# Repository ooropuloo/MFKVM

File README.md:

# MF KVM

**繁體中文** | [English](README.en.md)

MF KVM 是以 ESP32-P4 為主控、跑 [ESP-KVM](https://github.com/espkvm/espkvm) 韌體的 KVM over IP 小盒子：接上主機的 HDMI 和 USB 之後，就能透過 Wi-Fi 從瀏覽器看主機畫面、操作鍵盤滑鼠，也能按主機的電源和重置鍵。這個 repo 並列兩個設計：`off-the-shelf/` 用買得到的現成板組裝，只自製一片 ATX 小板；`lay-board/` 把所有電路自己布在一片 6 層板上。

**狀態：r8b 已於 2026-11-16 下單打板，板子還沒到。** 沒有焊過、沒有上電，通過的都是檔案和模型層級的檢查，沒有任何一項在硬體上驗證過。

授權見 [LICENSE](LICENSE)：硬體 CERN-OHL-P-2.0、程式 Apache-2.0、文件 CC-BY-4.0。第三方內容另依原本的條款，見 [THIRD_PARTY.md](THIRD_PARTY.md)。

## 目前版本：r8b

6 層單片板，40 × 40 mm，雙面放零件。主控是 ESP32-P4-Module（U1，組裝後手焊），影像用 TC358743（U7，BGA）。外殼是全鋁、無風扇，42 × 42 × 23 mm，Wi-Fi 天線外接。

| 外殼和尺寸 | 和 AA 電池比大小 |
|---|---|
|  |  |

**上面兩張和下面的爆炸圖是 AI 生成的示意圖，不是照片，東西還沒有做出來。** 它們是拿外殼的工程算繪當底圖重畫的，外形、開孔位置和標籤照著工程圖，尺寸標註是另外用程式畫上去的。螢幕畫面、板子上的小零件、材質和光影都是示意，細節以 [`case/stl/`](lay-board/r8b/case/stl/) 和 Gerber 為準。工程算繪在 [r8b 說明](lay-board/r8b/README.md)。

| 正面 | 背面 |
|---|---|
|  |  |

<details>
<summary>零件代號對照表（點開看圖查詢）</summary>

**正面（Top）**

| 代號 | 是什麼 | 用途／備註 |
|---|---|---|
| U1 | ESP32-P4 模組 | 主控加 Wi-Fi，另外買、組裝後手焊，最大熱源 |
| J3 | USB-C | 接被控主機（鍵盤滑鼠、虛擬媒體） |
| J5 | USB-C | 5 V 供電、燒錄、console |
| J6 | SM08B 8P | 接圓形 LCD |
| U14 | ESD 保護 | J5 的 USB 線 |
| U15 + L2 | 降壓 | 3V3 → 1.2 V |
| D1 | ESD 保護 | HDMI CEC |

**背面（Bottom）**

| 代號 | 是什麼 | 用途／備註 |
|---|---|---|
| J2 | HDMI | 影像輸入 |
| U7 | TC358743 BGA | HDMI 轉 CSI，最燙的晶片 |
| J7 | microSD | 虛擬媒體、儲存 |
| U16 | TPS259531 eFuse | 5 V 輸入保護，下單要核對方向 |
| U2 + L1 | 降壓 | 5 V → 3V3 |
| U4 | LDO | 3V3 → 2.5 V |
| U6 | TCA9517A | HDMI DDC 準位轉換 |
| U3、U8、U9 | ESD 保護 | J3 的 USB 線、HDMI TMDS |
| U10、U11、U12 | 光耦 | ATX 電源、重置、LED |
| J4 | SM06B 6P | 接 ATX 前面板 |
| J8 | U.FL | 接 Wi-Fi 天線（用線接到外殼上的 SMA 座） |
| Y1 | 27 MHz 振盪器 | U7 的時脈 |
| Q1 | P 通道 MOSFET | microSD 電源開關 |
| R68 + C72、C73 | 0.47 Ω 加兩顆 22 µF | 5 V 阻尼，取代 r7f 的 330 µF C69 |

電阻、電容太多沒有列，完整清單見 [`BOM_JLC.csv`](lay-board/r8b/fab_r8b/BOM_JLC.csv)。

</details>

板子的兩張圖是從板檔算繪的，不是照片。板檔沒有 3D 模型，零件是依外形和高度畫的方塊。

爆炸示意圖（AI 生成）。由上到下是上蓋、圓形 LCD、鋁散熱板、電路板、底殼。螢幕的線穿過散熱板的方孔接到板子角落的 J6。

| 項目 | 規格 |
|---|---|
| 板子 | 40 × 40 mm，6 層，1.2 mm，JLC06121H-3313，三顆安裝孔 |
| 外殼 | 42 × 42 × 23 mm，6061 鋁 CNC、黑色陽極，無風扇 |
| 表面溫度（模型） | 室溫 25 °C、一般負載下最高約 51.5 °C |
| 主控 | ESP32-P4-Module 基本款（SKU 28101，16MB、天線從焊盤引出），內建 ESP32-C6，2.4 GHz Wi-Fi |
| 天線 | 板上 U.FL，轉 SMA 到外殼左牆，外接天線 |
| 影像 | TC358743XBG，HDMI 轉 CSI |
| 螢幕 | 1.28 吋圓形 LCD（選配） |
| 供電 | Type-C，要能供 1.5 A 以上 |
| 打板包 | [`lay-board/r8b/fab_r8b/`](lay-board/r8b/fab_r8b/)，Gerber zip sha256 開頭 `3613530e` |

### 這版改了什麼（相對 r7f）

| 項目 | 改了什麼 |
|---|---|
| 板子尺寸 | 40 × 45 → 40 × 40 mm，安裝孔 4 顆 → 3 顆 |
| 5 V 阻尼 | 拿掉 330 µF 的 C69，R68 改成 0.47 Ω，新增 C72、C73（22 µF 0805） |
| 外殼 | 由「鋁上蓋＋塑膠底殼＋外接風扇導管」改成全鋁、無風扇，42 × 42 × 23 mm |
| 天線（r8b） | 改外接：外殼左牆開 SMA 孔，U.FL 轉 SMA 線接板子背面的 J8 |
| 板邊淨空（r8b） | SD_CMD 的兩顆過孔和 ATX_LED 走線往板內移到離板邊 0.40 mm 以上 |
| 高度夾持（r8b） | 上蓋的柱子不再壓板子，改用泡棉墊圈 |
| HDMI 開孔（外殼，2026-11-16） | 由矩形改成 HDMI 座的外形，上窄下寬（座焊在板子背面）。板子沒有改 |

TMDS、CSI、USB 的走線和 r7f 相同；r8 → r8b 零件位置、BOM、CPL 都沒有變，108 個網路只有 4 個的銅不同。

**板廠生產時改了阻抗線的線寬：** 100 Ω 線 5.0/7.8 → 4.7/8.1 mil，USB 90 Ω 線寬 7.09 → 6.37 mil，中心距和疊構不變。所以實體板的這幾條線和 repo 裡的 Gerber 不同。用本專案的解算器代回去，都還在 ±10 % 內，見 [`IMPEDANCE_AS_BUILT.md`](lay-board/r8b/IMPEDANCE_AS_BUILT.md)。

### 驗證到哪裡

| 已通過（檔案和模型層級） | 結果 |
|---|---|
| ERC、DRC | ERC 通過；DRC 0 錯誤、0 未連線，29 個警告逐項接受 |
| 電氣規則、熱插拔、輸入濾波、參考層、差動對間距、CSI 過孔、手焊間距、阻抗、零件本體 | 全部通過 |
| 板子故意放錯測試 | 124 項全部抓到 |
| 外殼幾何 | 126 項通過；故意放錯 25 項（含對照組）全部符合預期 |
| 獨立複審（r8） | 板子有條件可送；外殼的 1 項嚴重、3 項主要問題在 r8b 處理或由使用者裁決結案。r8b 沒有再做一次獨立複審 |

**沒有驗證：** 還沒有實體板，EMI、RF／RSSI、影像、USB、Wi-Fi、溫度都沒測過。熱模型在 r8b 沒有重跑。韌體只編譯過，沒有燒過。天線線、天線、泡棉墊圈、導熱材料都還沒選定料號。

**現在的進度：** 2026-11-16 下單，等板子。到貨後照 [`BRINGUP_CHECKLIST.md`](lay-board/r8b/BRINGUP_CHECKLIST.md) 上電。

**完整資料：** [r8b 說明](lay-board/r8b/README.md)、[R8B 改版報告](lay-board/r8b/R8B_REPORT.md)、[R8 改版報告](lay-board/r8b/R8_REPORT.md)、[獨立複審](lay-board/r8b/REVIEW_r8.md)、[熱分析](lay-board/r8b/thermal/THERMAL_R8.md)。上一版 r7f 的資料留在 [`lay-board/r7f/`](lay-board/r7f/README.md)。

## 較早的設計（ARCHIVE）

以下保留當時的內容當紀錄，都不是目前版本。`lay-board/` 這欄是 r5，那張單已經取消。

| | [`off-the-shelf/`](off-the-shelf/README.md)（現成料，第三版） | [`lay-board/`](lay-board/README.md)（客製板，第二版 r5） |
|---|---|---|
| **外殼尺寸** | 75.0 × 38.05 × 26.73 mm | 44 × 44 × 20 mm |
| **體積** | 76 cm³ | 39 cm³ |
| **買什麼** | DFRobot FireBeetle 2 ESP32-P4（DFR1172）、Geekworm C790、Waveshare 1.9 吋 LCD、Würth 50 mm 15-pin 排線（接點異面、同面各 1）、改過不接 VBUS 的 USB 線、Ø0.64 銅線、JST SH 線、螺絲、5 V 電源 | Waveshare ESP32-P4-Module-U（IPEX）、FPC 天線、1.28 吋圓形 LCD、自製 SHR-08 和 SHR-06 線、M2 × 16 螺絲 4 支 |
| **打什麼板** | 2 層 ATX 小板 rev B，11.05 × 35.4 mm（`fab_atx_b/`），尚未下單 | 6 層 40 × 40 mm 主板加雙面 PCBA，含 BGA（`fab_r5/`），JLC 審查中、未付款 |
| **印什麼** | 底殼、上蓋、C790 橋架、排線捲線棒、ATX 焊接墊片（建議 PETG） | 底殼、上蓋 |
| **韌體** | ESP-KVM `0893eef`，加 ST7789 修補與 ATX 修補（兩支 patch），只編譯過 | ESP-KVM `0893eef`，加開機預設值修補與 ATX 修補（兩支 patch），只編譯過。ATX 預設關閉，到 console 打開，見 `lay-board/firmware/BUILD_v2.md` |
| **主要風險** | 排線斜捲 45° 沒人測過、回報僅約 9 fps、ATX 小板焊死後要斜著裝 | 首版 6 層加 BGA 有錯就要重打、阻抗只有公式估算、最壞公差有 4 對本體可能相碰 |
| **狀態** | 只有設計，零件未買 | 打板包只能送 CAM 預審，還不能算放行 |
| **什麼時候選它** | 想先驗證功能、不想打 6 層板和焊 BGA、接受比較大的盒子。目前建議當驗證機，也能先驗證兩邊共用的韌體 | 要最小的外形，或要走正式小型產品，且願意承擔首版改板 |

每個設計的 README 都有 **「還缺什麼」** 清單，列出下單前和實機要做的事：[off-the-shelf](off-the-shelf/README.md#還缺什麼)、[lay-board](lay-board/README.md#還缺什麼)。

## 3D 頁面

每個資料夾裡有一份 HTML，下載後用瀏覽器開就能看（3D 需要連上網路載入 three.js）：

| 設計 | 檔案 |
|---|---|
| lay-board | [`lay-board/kvm-mini.html`](lay-board/kvm-mini.html) |
| off-the-shelf | [`off-the-shelf/v3.html`](off-the-shelf/v3.html) |

## 不在這個 repo 的東西

- **第一版（NANO 模組疊自製底板）：** 排針位置錯，已放棄，沒有放進來。
- **舊打板包：** `fab`、`fab_new`、`fab_r2`～`fab_r4`、`fab_atx` 都不能用，原因寫在各 README。
- **建置輸出：** ESP-KVM clone、build 目錄、映像檔、建置 log。重新編譯的方法在各 README。
- **第三方原始檔：** NANO 官方 CAD、ExoAnchor 壓縮檔、FireBeetle STEP。來源見 [THIRD_PARTY.md](THIRD_PARTY.md) 和 `off-the-shelf/research/`。

## 常用檢查（在 repo 根目錄）

```sh
python lay-board/tools/maskcheck.py lay-board/fab_r5/p4_kvm_mini_gerber.zip
python lay-board/tools/holecheck.py lay-board/fab_r5/p4_kvm_mini_gerber.zip
sh lay-board/tools/check.sh out/final.ses     # 要 KiCad，路徑用 KICAD_CLI、KICAD_TOOL_HOME 覆寫
python lay-board/tools/bodycheck.py lay-board/out
python lay-board/tools/maskcheck.py off-the-shelf/fab_atx_b/mf_kvm_atx_gerber.zip
python lay-board/tools/holecheck.py off-the-shelf/fab_atx_b/mf_kvm_atx_gerber.zip
```

`.gitattributes` 設定 `* -text`，檔案逐位元組保存，不轉換行尾，所以 Gerber 雜湊不會變，`.sh` 也不會變成 CRLF。

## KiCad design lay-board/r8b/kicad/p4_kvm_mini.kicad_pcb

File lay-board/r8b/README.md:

# MF KVM lay-board r8b

目前的板子版本。6 層 40 × 40 mm，ESP32-P4-Module（U1，手焊）加 TC358743（U7，BGA）。r8 由 r7f 改版，把板子從 40 × 45 縮到 40 × 40 mm，外殼改成全鋁、無風扇、42 × 42 × 23 mm；r8b 再把三處走線往板內移、天線改外接。

**狀態：2026-11-16 已下單打板，板子還沒到。** 沒有焊過、沒有上電，通過的都是檔案和模型層級的檢查，沒有任何一項在實機驗證過。

**實體板有一處和這裡的 Gerber 不同：** 板廠審核時把阻抗線改細、中心距不變（100 Ω 線 5.0/7.8 → 4.7/8.1 mil，USB 90 Ω 線寬 7.09 → 6.37 mil）。數字和核對結果在 [`IMPEDANCE_AS_BUILT.md`](IMPEDANCE_AS_BUILT.md)。

| 項目 | 值 |
|---|---|
| Gerber zip sha256 | `3613530e5c3256c378794c367a53c94c30cd249da4c4403c4d094f22236d9397` |
| 外形 | 40.0 × 40.0 mm，四角 1.5 mm 倒角，三顆 2.2 mm 鍍通安裝孔 |
| 層數、厚度 | 6 層，1.2 mm，外層 1 oz |
| 疊構 | JLC06121H-3313，阻抗控制 |
| 最小線寬線距 | 0.09 mm |
| 過孔 | 0.4 / 0.2 mm，Epoxy Filled & Capped |
| 絲印版本 | R8B |
| 供電 | Type-C，要能供 1.5 A 以上 |

每次重跑 release，zip 的 sha 都會變，設計沒有改也一樣。判斷兩包是否相同要用 `tools/gerber_equal.py` 比幾何。

## 圖

### 示意圖（AI 生成）

| 外殼和尺寸 | 和 AA 電池比大小 |
|---|---|
|  |  |

**這三張是 AI 生成的示意圖，不是照片，也不是從 CAD 直接算繪的。** 做法是拿下面的工程算繪當底圖，請生圖模型重畫成棚拍質感；尺寸標註是另外用程式畫上去的。對照過的項目：外形比例、上蓋和底殼之間的銀色分隔線、SMA 座和 USB-C 開孔的位置、各面的標籤、爆炸圖的疊放順序、螢幕的線穿過散熱板方孔接到 J6、兩個 USB-C 座分在左邊和前緣。不準的地方：螢幕畫面是示意（不是實際韌體畫面，位址是範例）、板子上模組周圍的小零件不是逐顆對應、材質和光影是想像的。要看準確的幾何用下面的工程算繪、`case/stl/` 和 Gerber。

### 工程算繪

**下面都是電腦算繪，不是照片。** 板子還沒有做出來。零件是依外形尺寸和高度畫的方塊，顏色只用來分類。

| 正面 | 背面 |
|---|---|
|  |  |

| 外殼組裝 | 外殼爆炸 |
|---|---|
|  |  |

阻抗控制走線的位置：

## 和 r7f 的差別

- 板子 40 × 45 → 40 × 40 mm。安裝孔 4 顆 → 3 顆。
- 5 V 阻尼：330 µF 的 C69 拿掉，R68 改成 0.47 Ω，新增 C72、C73（22 µF 0805）。
- 外殼由「鋁上蓋＋塑膠底殼＋外接風扇導管」改成全鋁、無風扇。
- r8b：SD_CMD 的兩顆過孔和 ATX_LED 走線往板內移到離板邊 0.40 mm 以上；天線改外接，外殼左牆開 SMA 孔；上蓋的柱子不再壓板子，改用泡棉墊圈。
- 外殼追加修改（2026-11-16，板子沒改）：底殼前牆的 HDMI 開孔由矩形改成 HDMI 座的外形，上窄下寬，因為座焊在板子背面、倒掛在板子下方。切角尺寸原廠圖面沒有標，發加工前要量實物，見 `R8B_REPORT.md` 第 5b 節。
- TMDS、CSI、USB 的走線和 r7f 相同。

細節看 `R8_REPORT.md` 和 `R8B_REPORT.md`。

## U1：主控模組（不在打板的 BOM 裡，要另外買、自己手焊）

| 項目 | 值 |
|---|---|
| 廠牌、型號 | Waveshare（微雪）ESP32-P4-Module |
| SKU | 28101 |
| Flash 版本 | **16MB** |
| 天線版本 | **焊盤引出版**（英文站叫 Onboard IPEX connector = Without） |
| 模組內容 | ESP32-P4NRW32X（內含 32 MB PSRAM）加 ESP32-C6（2.4 GHz Wi-Fi、藍牙） |
| 尺寸、接腳 | 25 × 25 mm，城堡焊盤，腳距 1 mm，88 腳 |

同一個商品頁還有三個版本，都不要選：

| 版本 | 為什麼不要 |
|---|---|
| IPEX 接口版（ESP32-P4-Module-U） | 天線訊號改走模組上的 IPEX 座，不從焊盤出來，板子背面的 J8 會沒有訊號 |
| 32MB | 韌體是照 16 MB 編的，燒到 32 MB 模組沒有測過 |
| 32MB 加 IPEX | 上面兩個問題都有 |

板子把模組第 2 腳（LNA_OUT）用 50 Ω 走線拉到背面的 J8（U.FL 座），再用線接到外殼上的 SMA 天線。焊盤引出版的 RF 訊號經模組上的 **R99（0 Ω）** 送到第 2 腳，R99 不能拆。模組本身沒有天線，而 Wi-Fi 是這台唯一的網路。

### 板子用到的模組腳位

| 功能 | 模組腳位 → 網路名 |
|---|---|
| 電源 | 84、85、86 → 3V3；1、3、15、33、40、47、52、83 → GND；87 → ESP_EN |
| 天線 | 2 → LNA_OUT（到 J8） |
| HDMI 擷取（MIPI CSI，來自 TC358743） | 41／42 → CSI_D0_N／P；43／44 → CSI_CK_P／N；45／46 → CSI_D1_N／P |
| TC358743 控制 | 22 → I2C_SDA；23 → I2C_SCL；32 → TC_RST（GPIO 23） |
| USB 到被控主機（J3） | 48 → USB_DN；49 → USB_DP |
| USB 燒錄和 log（J5） | 50 → USB2_DN；51 → USB2_DP（GPIO 24／25） |
| microSD（J7） | 67–70 → SD_D0–D3；71 → SD_CLK；72 → SD_CMD；73 → SD_PWR_N（GPIO 45）；66 → LDO_VO4 |
| 圓形 LCD（J6） | 24 → LCD_DIN；25 → LCD_CLK；26 → LCD_CS；27 → LCD_DC；28 → LCD_RST（GPIO 9–13） |
| ATX（J4） | 19 → ATX_PWR（GPIO 4）；20 → ATX_RST（GPIO 5）；17 → ATX_LED（GPIO 2） |
| 其他 | 18 → HOST_VBUS_DIV；62 → BOOT（TP1）；64／65 → U0_TX／U0_RX（TP3／TP4）；4／5／9／10 → C6_RXD／TXD／IO9／IO8（測試點） |

### 手焊注意

- **第 24、25 腳不要拖焊**：旁邊緊貼 R80、R81（0201，33 Ω，焊盤間距 0.387 mm）。烙鐵不要往 J6 方向帶，錫從模組那一側收。
- **第 67–72 腳不要往板子左側拖**：R79 離第 70 腳約 1 mm。
- 焊完用放大鏡看 R80、R81 還在、沒有連錫或立碑。

## 板子以外還要準備的

| 項目 | 規格 | 備註 |
|---|---|---|
| U1 模組 | 見上一節 | 每片板一顆 |
| U.FL 轉 SMA 穿牆線 | U.FL（IPEX MHF1）對標準 SMA 母座，長約 50–100 mm | 外殼照六角 8 mm、孔 6.5 mm、壓接套管 Ø5 × 10 mm 設計。料號沒有選定 |
| 2.4 GHz 天線 | 標準 SMA 公頭，底座直徑不超過 10 mm | 不是 RP-SMA。料號沒有選定 |
| Type-C 電源 | 5 V，1.5 A 以上 | 1.0 A 以下的埠在全負載下起不來（`fab_r8b/coldstart_r8.txt`） |
| USB 轉 UART 線 | 3.3 V，115200 | 開機階段的 log 只從 UART0 測試點出來 |
| 圓形 LCD（選配） | GC9A01，240 × 240，接 J6 | 不接也能開機 |
| ATX 線（選配） | JST SH 1.0 mm 6 pin，接 J4 | 韌體預設關閉 ATX，量測過才接主機板 |
| 外殼 | 6061 鋁 CNC，圖檔在 `case/stl/` | 接觸面不陽極，清單在 `case/stl/case_spec.json` 的 `masked` |
| 螺絲、泡棉墊圈 | M2 × 16 三顆；墊圈外徑 3.6、內徑 2.2、厚 1.5 mm 三片 | 墊圈料號沒有選定 |
| 導熱材料 | 模組屏蔽罩上方的填充；TC358743 下方凸台的導熱墊（間隙約 0.5 mm） | 料號沒有選定 |

第一次上電的步驟在 [`BRINGUP_CHECKLIST.md`](BRINGUP_CHECKLIST.md)。它是照文件排的，還沒有在實機上走過。

## 內容

| 路徑 | 說明 |
|---|---|
| `R8_REPORT.md`、`R8B_REPORT.md` | 改版報告，先看 R8B |
| `REVIEW_r8.md` | 獨立複審 |
| `MUTATION_REPORT.txt` | 故意放錯測試結果 |
| `IMPEDANCE_AS_BUILT.md` | 阻抗線的設計值和板廠生產值 |
| `BRINGUP_CHECKLIST.md` | 到貨當天的檢查表 |
| `fab_r8b/` | 打板包：Gerber、BOM、CPL、佈局圖和線路圖 PDF、阻抗表、各項檢查輸出 |
| `kicad/` | KiCad 原始檔 |
| `case/` | 外殼產生與檢查程式、STL／STEP、算繪圖 |
| `firmware/` | 韌體建置說明與修補。不放編好的映像 |
| `thermal/` | 熱分析報告 |
| `report_r8/` | r7f→r8、r8→r8b 的差異比對，冷啟動圖 |
| `gen_mini.py`、`layout.py`、`tools/`、`data/` | 產生板子和跑檢查的程式、布線資料 |

`fab_r8b/README.md` 是打板時的說明，內容停在下單之前，請以本頁為準。

和 `r7f/` 比，這裡沒有 `pdf/` 那一套整理過的報告，也沒有 `out/` 的中間檔。

規格書版權屬原廠，沒有放在這裡。要重跑工具，用環境變數指定路徑：`KICAD_CLI`（預設 `kicad-cli`）、`KICAD_TOOL_HOME`、`FREEROUTING_JAR`、`CASE_PY`、`CHROME`。這些工具是從原本的工作目錄複製過來的，路徑改成環境變數後只做過語法檢查，沒有在這裡完整跑過。

## 下單時必做

- 貼片預覽核對 U16（eFuse）第 1 腳：底視圖左下角，靠 C71／R71／R72。轉 180° 會讓 VBUS 短路到 GND。
- 其他方向標為 UNKNOWN 的零件要逐顆看，對照 `fab_r8b/CPL_pin1_check.md` 和 `fab_r8b/CPL_polarity_pin1_r8.md`。
- 過孔選 Epoxy Filled & Capped，不要選阻焊塞孔。
- 拼板要自己指定：四個邊都有東西貼著板邊，後緣不要放郵票孔或 V-cut，郵票孔殘料不能凸出 40.00 mm 外形。

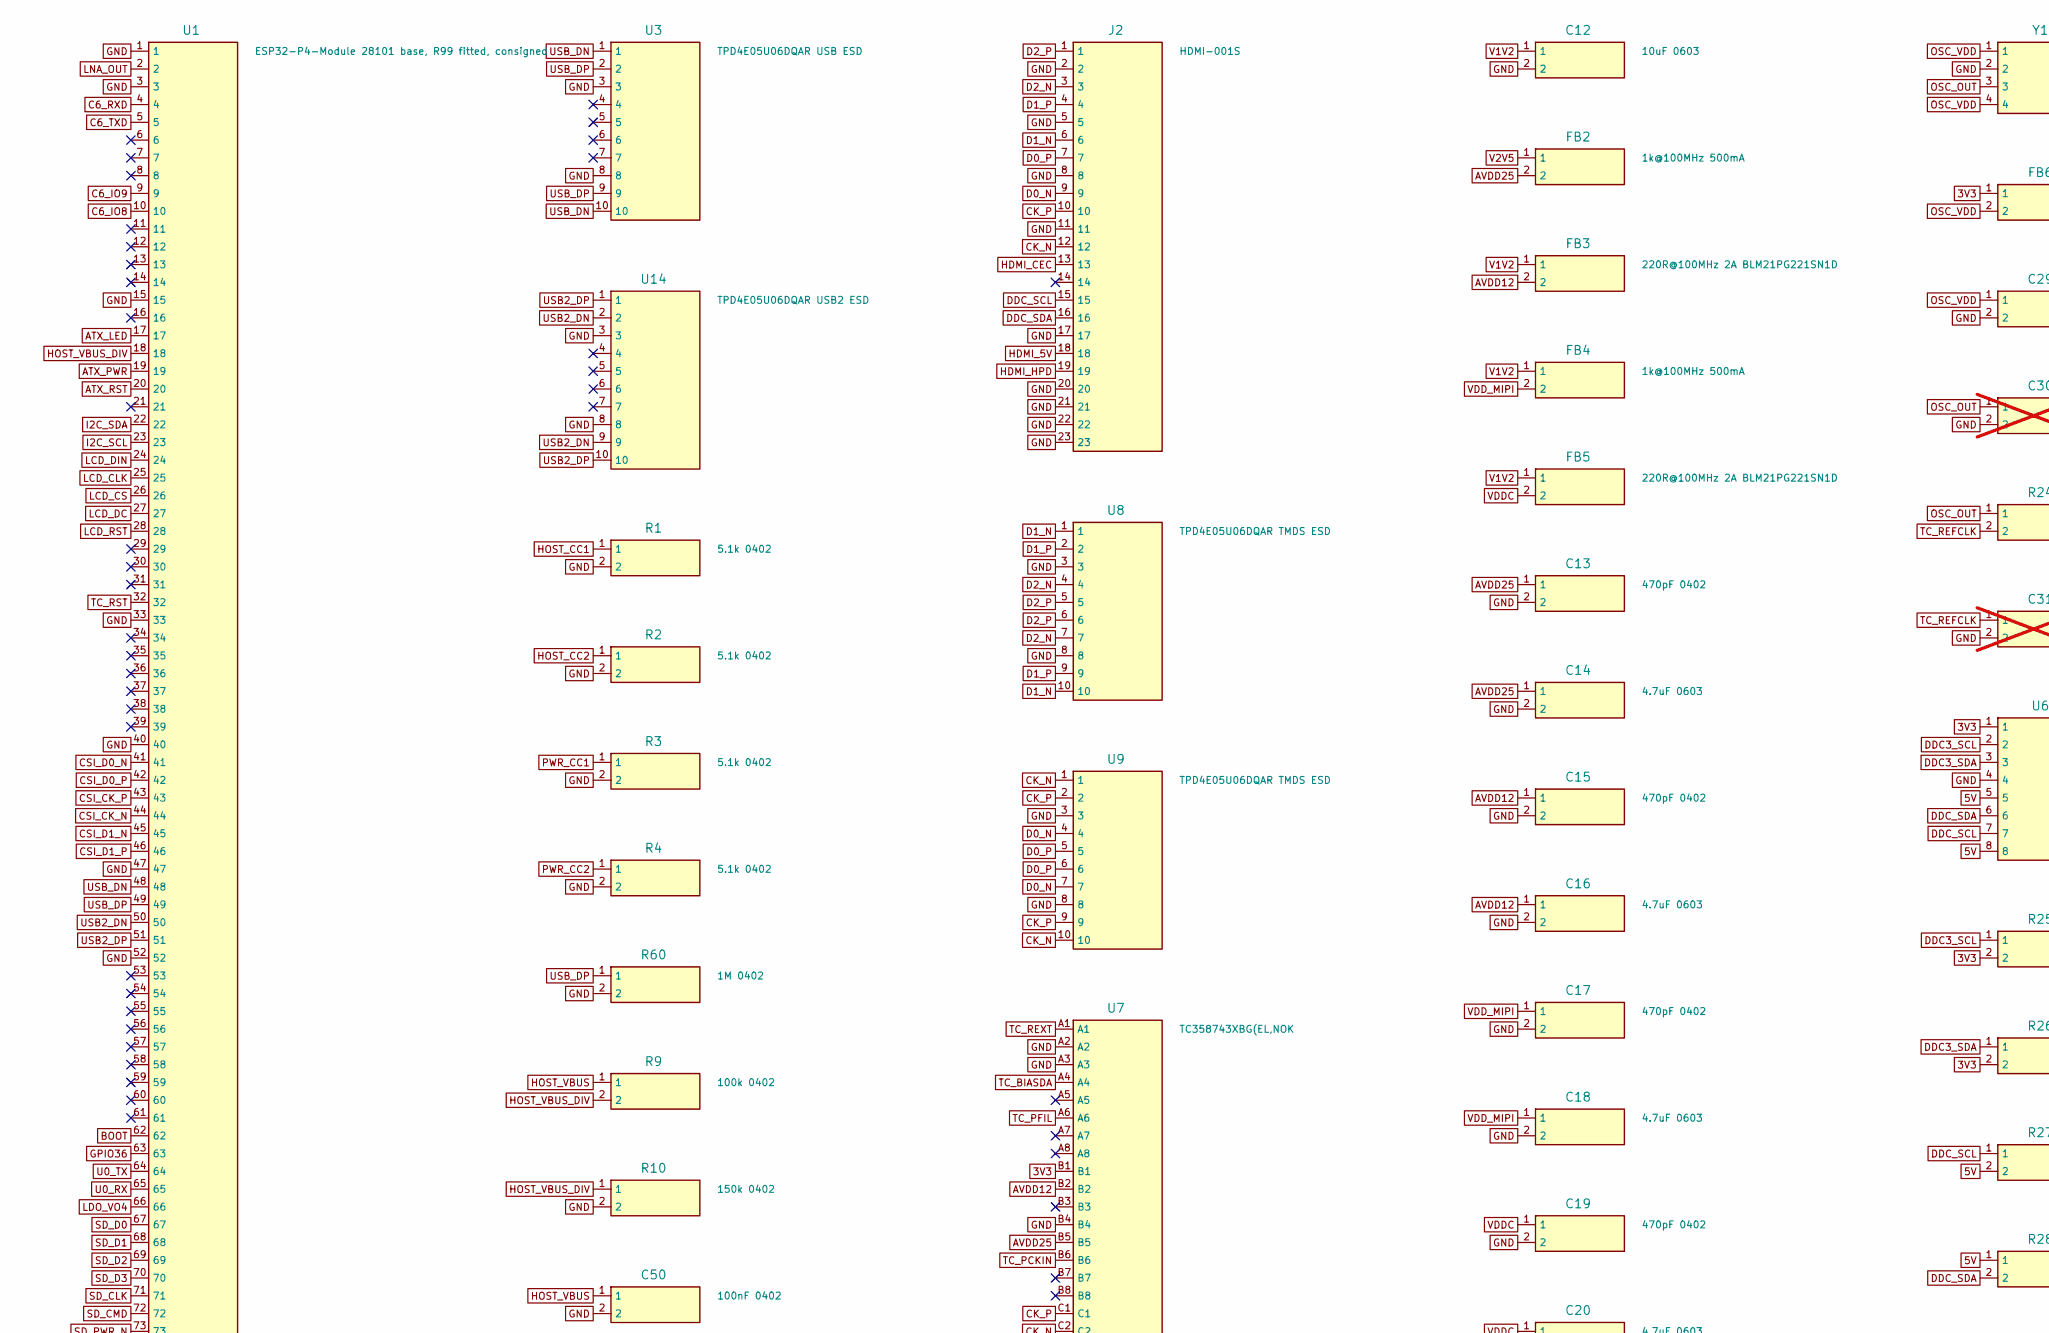
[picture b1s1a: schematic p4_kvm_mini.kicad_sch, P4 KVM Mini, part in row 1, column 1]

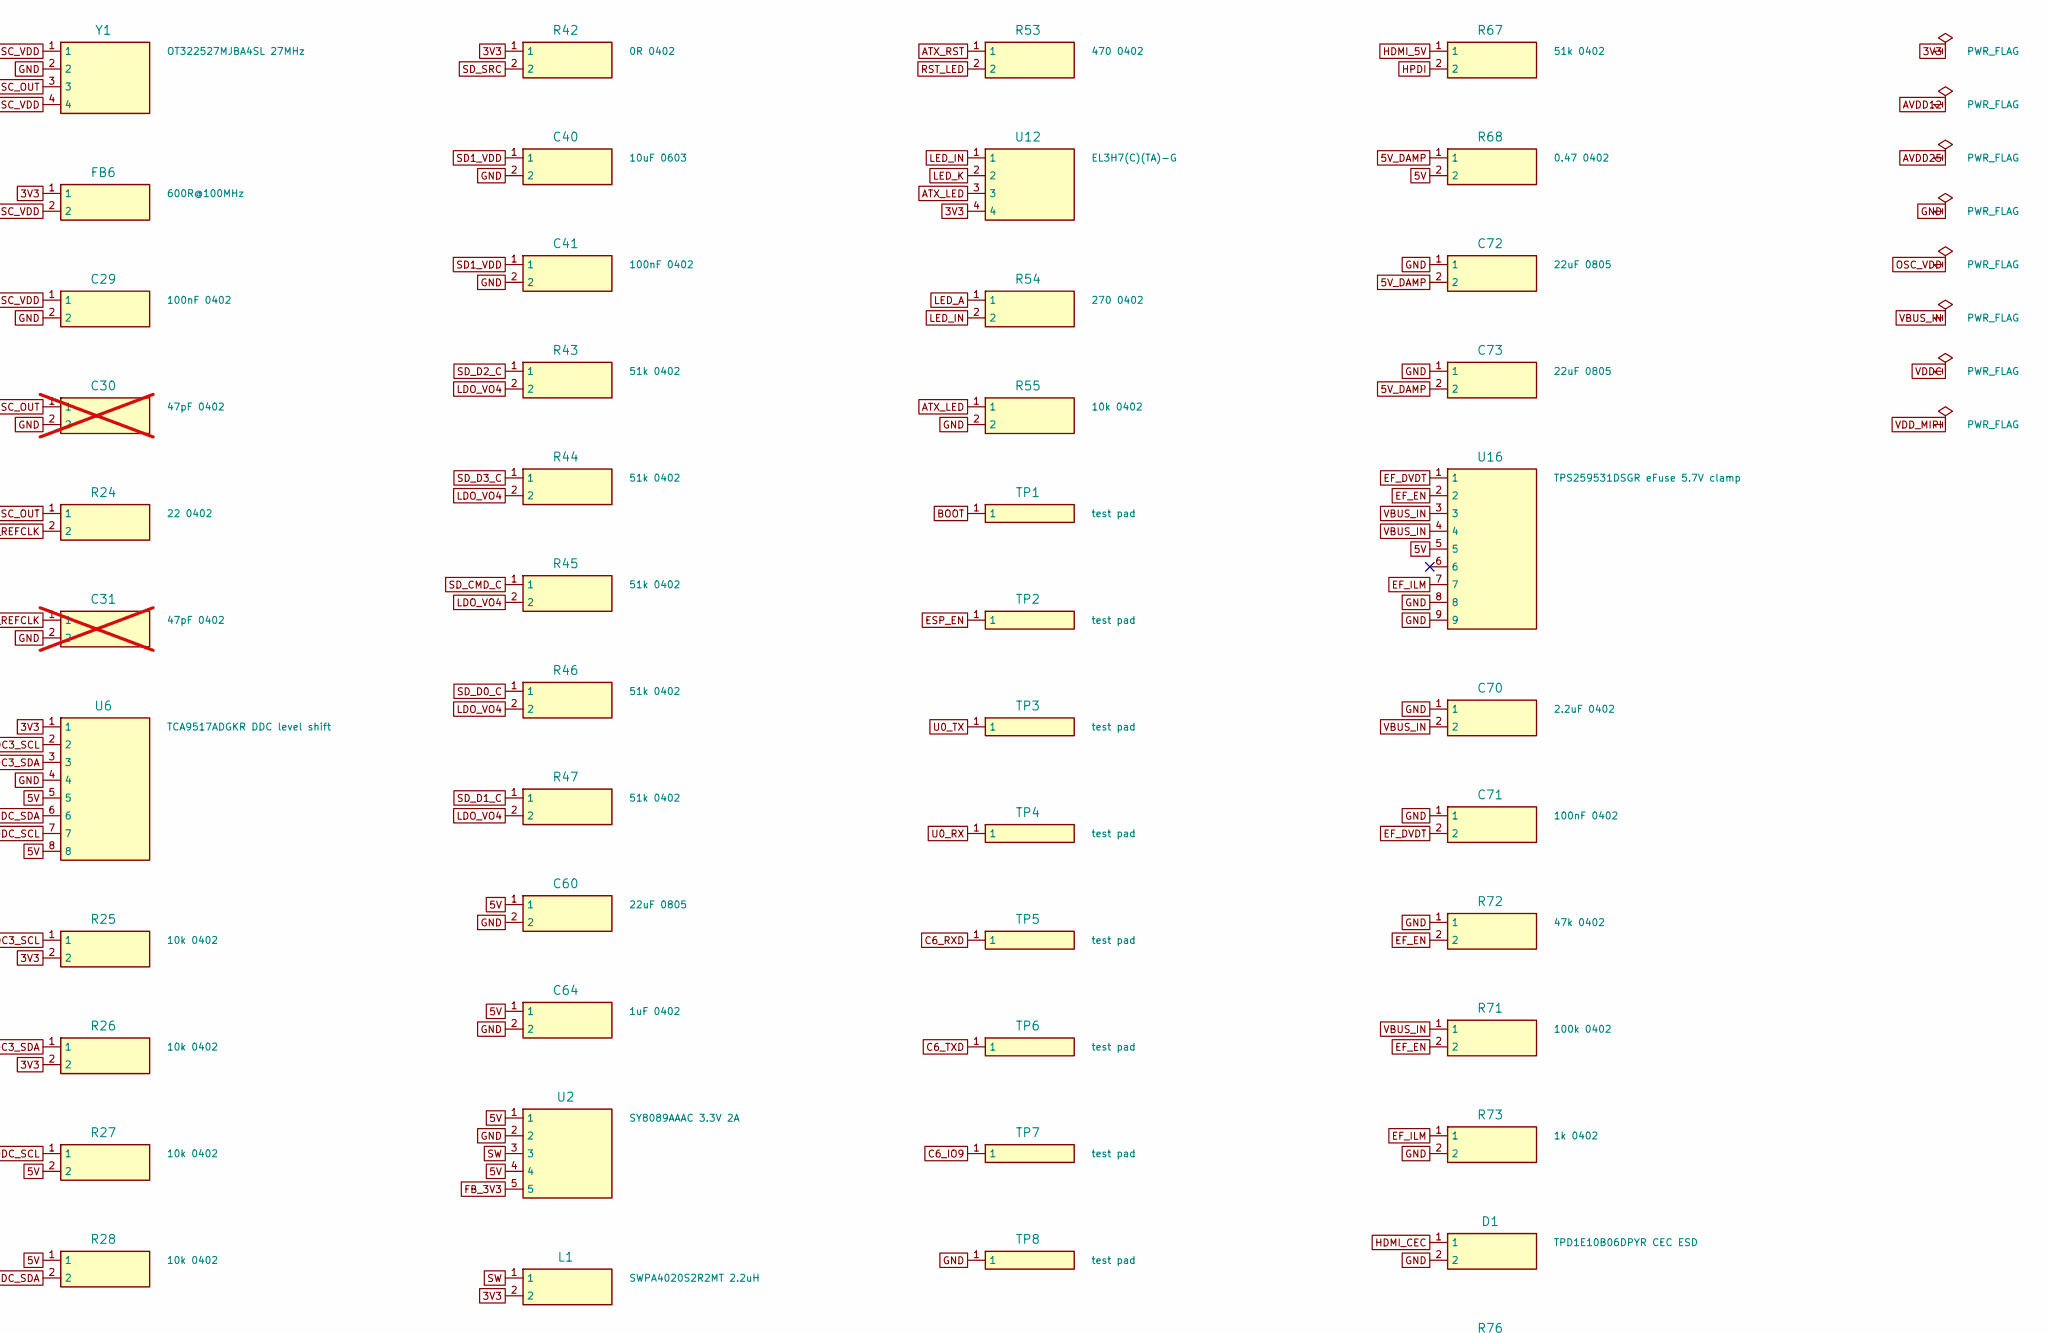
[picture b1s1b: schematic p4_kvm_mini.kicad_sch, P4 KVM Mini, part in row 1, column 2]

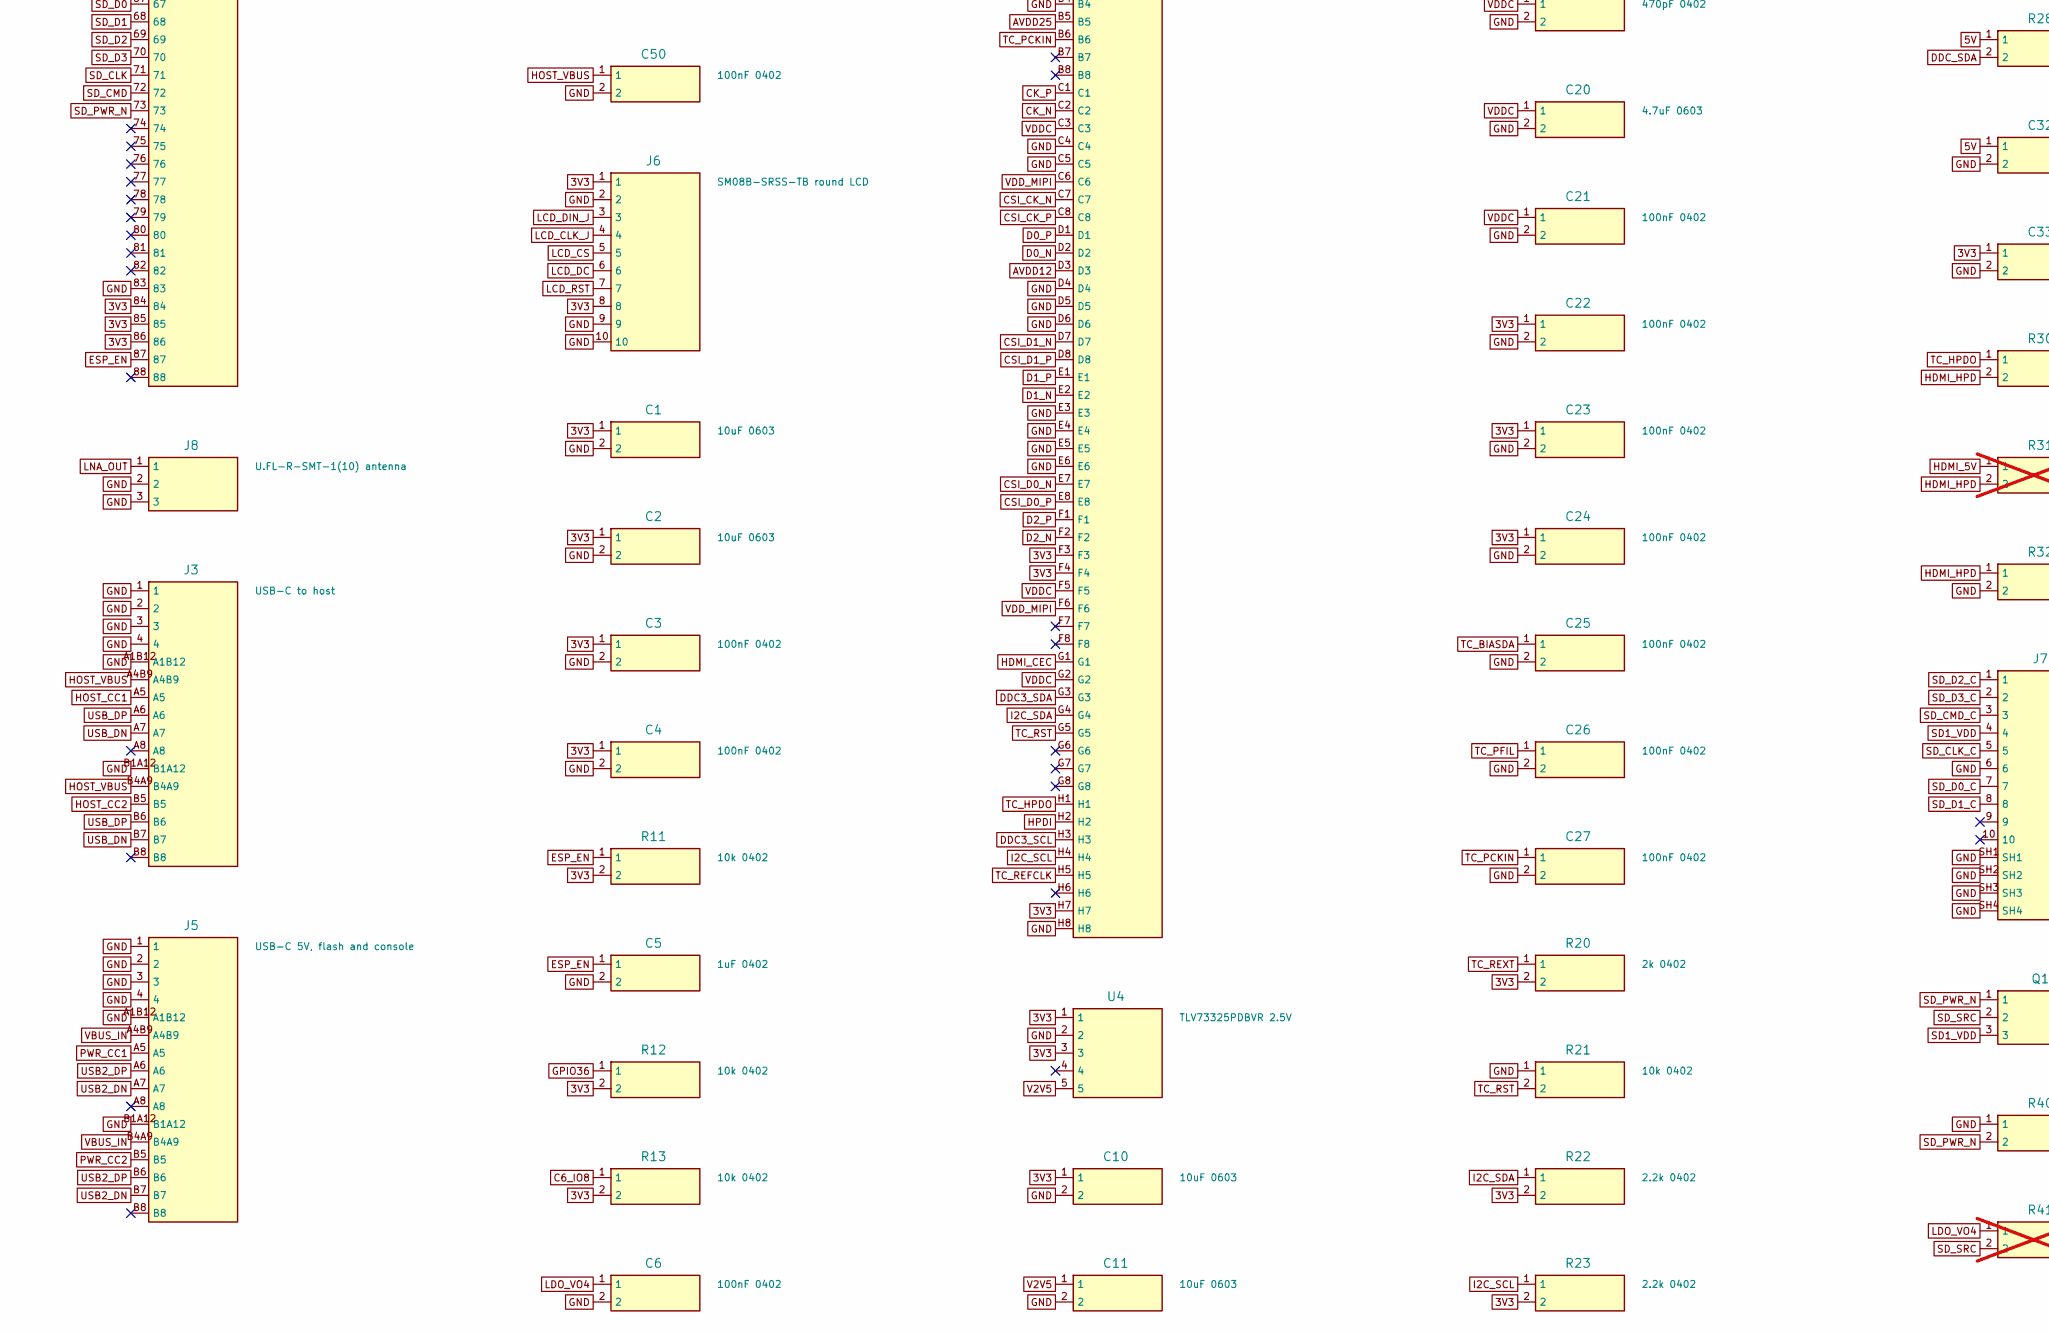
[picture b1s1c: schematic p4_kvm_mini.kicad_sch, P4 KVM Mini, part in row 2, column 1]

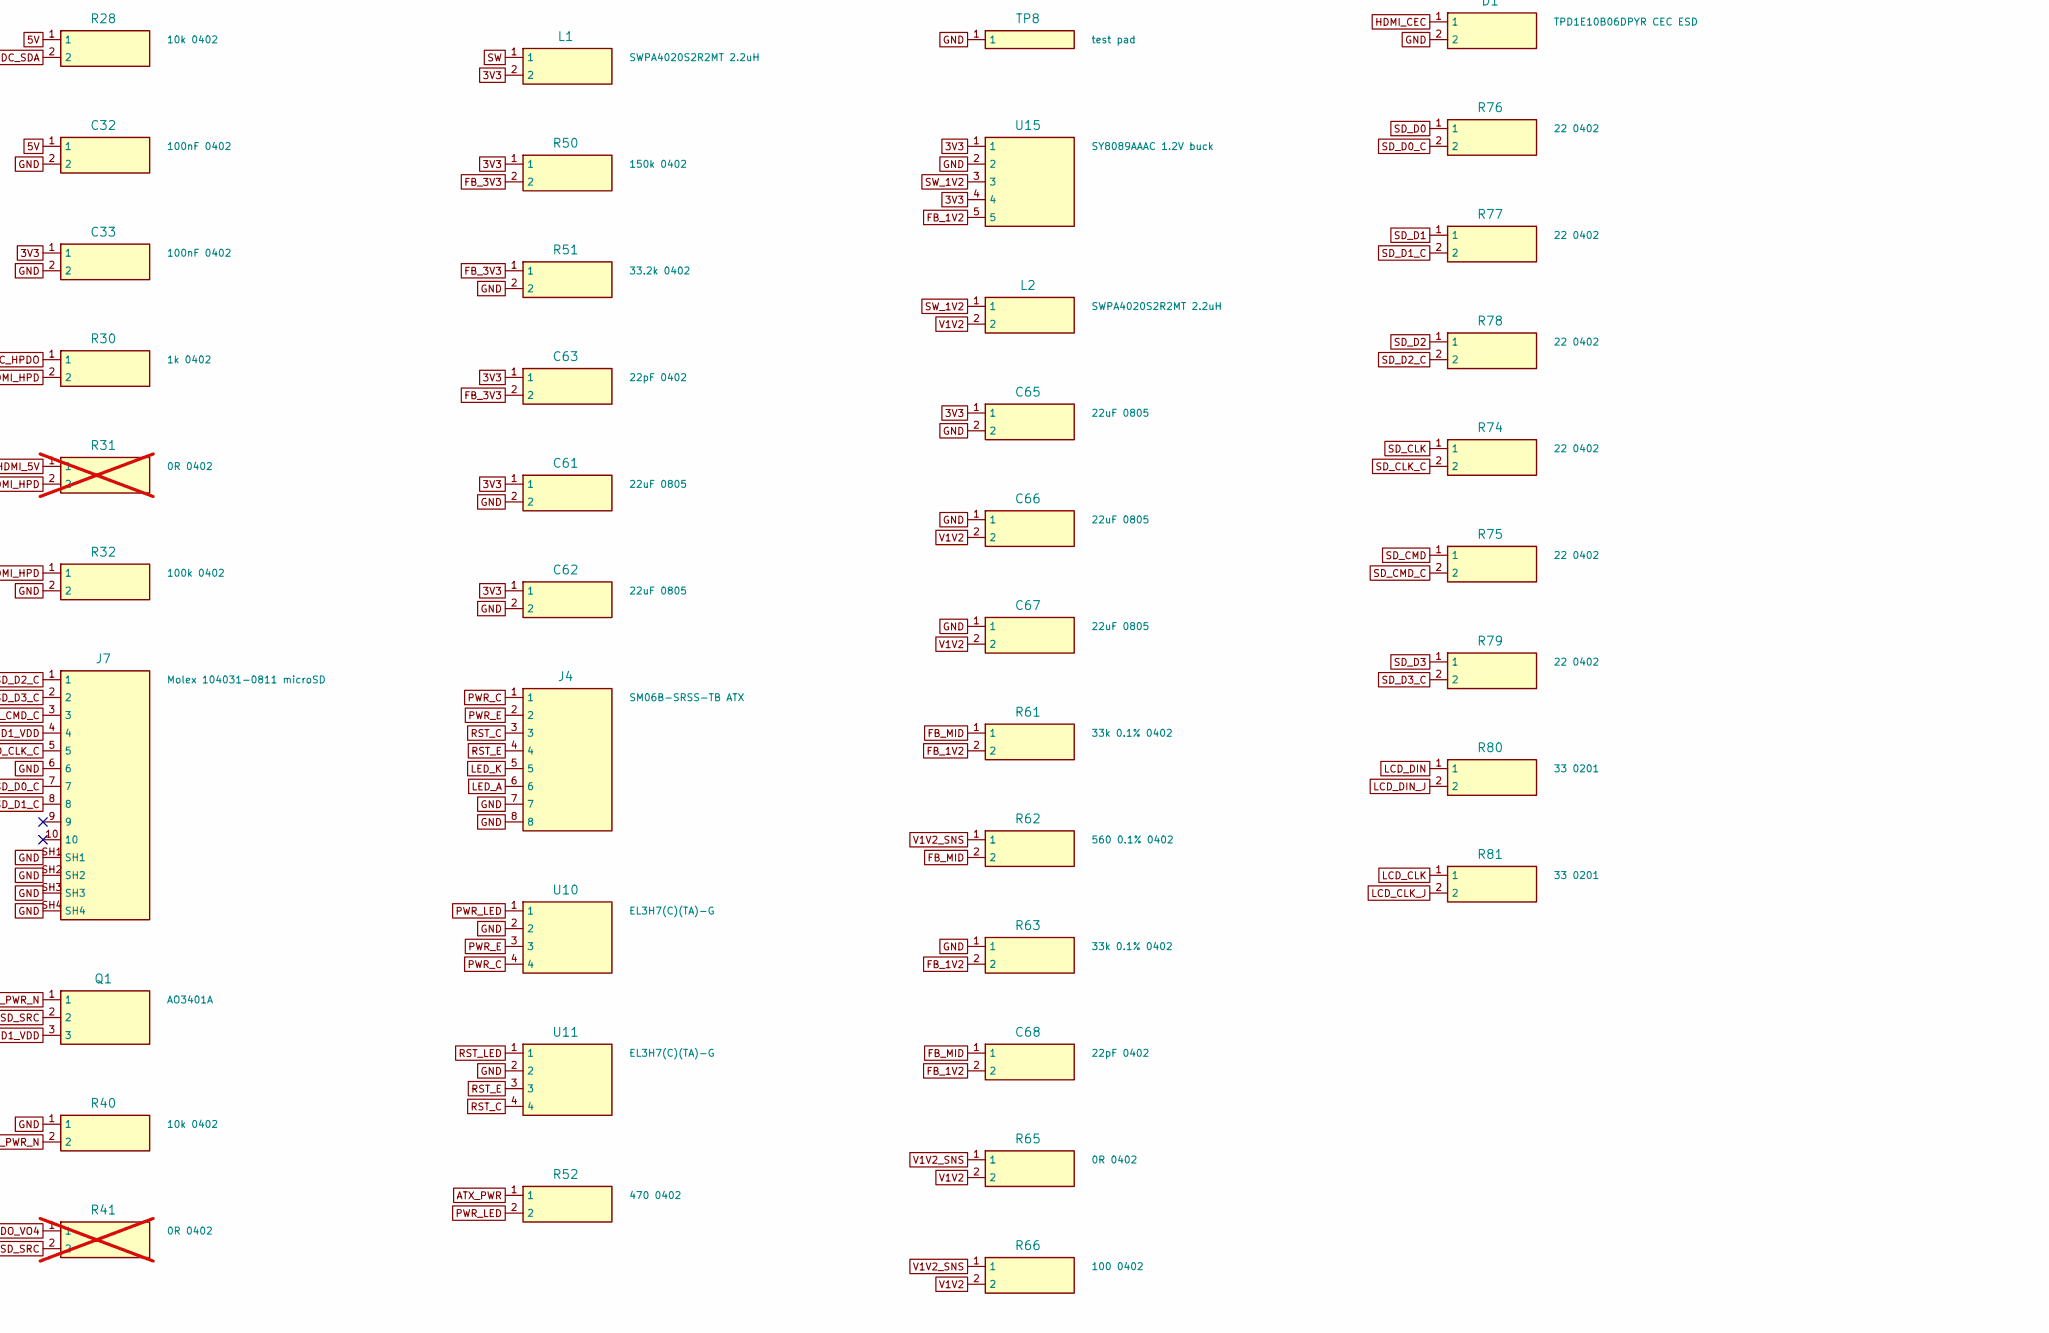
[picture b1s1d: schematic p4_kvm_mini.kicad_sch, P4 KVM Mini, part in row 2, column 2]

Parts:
C1, C2, C10, C11, C12, C40: 10uF 0603; C0603; LCSC C19702
C3, C4, C6, C21, C22, C23, C24, C25, C26, C27, C29, C32, C33, C41, C50, C71: 100nF 0402; R0402; LCSC C1525
C5, C64: 1uF 0402; R0402; LCSC C52923
C13, C15, C17, C19: 470pF 0402; R0402; LCSC C1537
C14, C16, C18, C20: 4.7uF 0603; C0603; LCSC C19666
C30, C31: 47pF 0402; R0402; LCSC C1567; not fitted
C60, C61, C62, C65, C66, C67, C72, C73: 22uF 0805; C0805; LCSC C45783
C63, C68: 22pF 0402; R0402; LCSC C1555
C70: 2.2uF 0402; R0402; LCSC C385032
D1: TPD1E10B06DPYR CEC ESD; X1SON-2_0.6x1; LCSC C48260
FB2, FB4: 1k@100MHz 500mA; C0805; LCSC C98485
FB3, FB5: 220R@100MHz 2A BLM21PG221SN1D; C0805; LCSC C85840
FB6: 600R@100MHz; C0603; LCSC C19330
J2: HDMI-001S; LCSC C720616
J3: USB-C to host; USB-C_HX_16P; LCSC C41427493
J4: SM06B-SRSS-TB ATX; JST_SM06B; LCSC C160405
J5: USB-C 5V, flash and console; USB-C_HX_16P; LCSC C41427493
J6: SM08B-SRSS-TB round LCD; JST_SM08B; LCSC C160407
J7: Molex 104031-0811 microSD; microSD_Molex_104031-0811; LCSC C585350
J8: U.FL-R-SMT-1(10) antenna; U.FL-R-SMT-1; LCSC C88373
L1, L2: SWPA4020S2R2MT 2.2uH; IND4020; LCSC C83423
Q1: AO3401A; SOT-23; LCSC C15127
R1, R2, R3, R4: 5.1k 0402; R0402; LCSC C25905
R9, R32, R71: 100k 0402; R0402; LCSC C25741
R10, R50: 150k 0402; R0402; LCSC C25755
R11, R12, R13, R21, R25, R26, R27, R28, R40, R55: 10k 0402; R0402; LCSC C25744
R20: 2k 0402; R0402; LCSC C4109
R22, R23: 2.2k 0402; R0402; LCSC C25879
R24, R74, R75, R76, R77, R78, R79: 22 0402; R0402; LCSC C25092
R30, R73: 1k 0402; R0402; LCSC C11702
R31, R41: 0R 0402; R0402; LCSC C17168; not fitted
R42, R65: 0R 0402; R0402; LCSC C17168
R43, R44, R45, R46, R47, R67: 51k 0402; R0402; LCSC C25794
R51: 33.2k 0402; R0402; LCSC C122548
R52, R53: 470 0402; R0402; LCSC C25117
R54: 270 0402; R0402; LCSC C25099
R60: 1M 0402; R0402; LCSC C26083
R61, R63: 33k 0.1% 0402; R0402; LCSC C728559
R62: 560 0.1% 0402; R0402; LCSC C319512
R66: 100 0402; R0402; LCSC C25076
R68: 0.47 0402; R0402; LCSC C423162
R72: 47k 0402; R0402; LCSC C25792
R80, R81: 33 0201; R0201; LCSC C320843
TP1, TP2, TP3, TP4, TP5, TP6, TP7, TP8: test pad; TP_1.0
U1: ESP32-P4-Module 28101 base, R99 fitted, consigned; ESP32-P4-Module
U2: SY8089AAAC 3.3V 2A; SOT-23-5; LCSC C78988
U3: TPD4E05U06DQAR USB ESD; USON-10; LCSC C138714
U4: TLV73325PDBVR 2.5V; SOT-23-5; LCSC C882825
U6: TCA9517ADGKR DDC level shift; MSOP-8; LCSC C201698
U7: TC358743XBG(EL,NOK; BGA-64_6x6; LCSC C3008606
U8, U9: TPD4E05U06DQAR TMDS ESD; USON-10; LCSC C138714
U10, U11, U12: EL3H7(C)(TA)-G; SSOP-4_1.27; LCSC C92243
U14: TPD4E05U06DQAR USB2 ESD; USON-10; LCSC C138714
U15: SY8089AAAC 1.2V buck; SOT-23-5; LCSC C78988
U16: TPS259531DSGR eFuse 5.7V clamp; WSON-8_2x2_EP; LCSC C2155674
Y1: OT322527MJBA4SL 27MHz; OSC3225; LCSC C725995

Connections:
3V3: C1.1, C2.1, C3.1, C4.1, C10.1, C22.1, C23.1, C24.1, C33.1, C61.1, C62.1, C63.1, C65.1, FB6.1, J6.1, J6.8, L1.2, R11.2, R12.2, R13.2, R20.2, R22.2, R23.2, R25.2, R26.2, R42.1, R50.1, U1.84, U1.85, U1.86, U4.1, U4.3, U6.1, U7.B1, U7.F3, U7.F4, U7.H7, U12.4, U15.1, U15.4
5V: C32.1, C60.1, C64.1, R27.2, R28.1, R68.2, U2.1, U2.4, U6.5, U6.8, U16.5
5V_DAMP: C72.2, C73.2, R68.1
ATX_LED: R55.1, U1.17, U12.3
ATX_PWR: R52.1, U1.19
ATX_RST: R53.1, U1.20
AVDD12: C15.1, C16.1, FB3.2, U7.B2, U7.D3
AVDD25: C13.1, C14.1, FB2.2, U7.B5
BOOT: TP1.1, U1.62
C6_IO8: R13.1, U1.10
C6_IO9: TP7.1, U1.9
C6_RXD: TP5.1, U1.4
C6_TXD: TP6.1, U1.5
CK_N: J2.12, U7.C2, U9.1, U9.10
CK_P: J2.10, U7.C1, U9.2, U9.9
CSI_CK_N: U1.44, U7.C7
CSI_CK_P: U1.43, U7.C8
CSI_D0_N: U1.41, U7.E7
CSI_D0_P: U1.42, U7.E8
CSI_D1_N: U1.45, U7.D7
CSI_D1_P: U1.46, U7.D8
D0_N: J2.9, U7.D2, U9.4, U9.7
D0_P: J2.7, U7.D1, U9.5, U9.6
D1_N: J2.6, U7.E2, U8.1, U8.10
D1_P: J2.4, U7.E1, U8.2, U8.9
D2_N: J2.3, U7.F2, U8.4, U8.7
D2_P: J2.1, U7.F1, U8.5, U8.6
DDC3_SCL: R25.1, U6.2, U7.H3
DDC3_SDA: R26.1, U6.3, U7.G3
DDC_SCL: J2.15, R27.1, U6.7
DDC_SDA: J2.16, R28.2, U6.6
EF_DVDT: C71.2, U16.1
EF_EN: R71.2, R72.2, U16.2
EF_ILM: R73.1, U16.7
ESP_EN: C5.1, R11.1, TP2.1, U1.87
FB_1V2: C68.2, R61.2, R63.2, U15.5
FB_3V3: C63.2, R50.2, R51.1, U2.5
FB_MID: C68.1, R61.1, R62.2
GND: C1.2, C2.2, C3.2, C4.2, C5.2, C6.2, C10.2, C11.2, C12.2, C13.2, C14.2, C15.2, C16.2, C17.2, C18.2, C19.2, C20.2, C21.2, C22.2, C23.2, C24.2, C25.2, C26.2, C27.2, C29.2, C30.2, C31.2, C32.2, C33.2, C40.2, C41.2, C50.2, C60.2, C61.2, C62.2, C64.2, C65.2, C66.1, C67.1, C70.1, C71.1, C72.1, C73.1, D1.2, J2.2, J2.5, J2.8, J2.11, J2.17, J2.20, J2.21, J2.22, J2.23, J3.1, J3.2, J3.3, J3.4, J3.A1B12, J3.B1A12, J4.7, J4.8, J5.1, J5.2, J5.3, J5.4, J5.A1B12, J5.B1A12, J6.2, J6.9, J6.10, J7.6, J7.SH1, J7.SH2, J7.SH3, J7.SH4, J8.2, J8.3, R1.2, R2.2, R3.2, R4.2, R10.2, R21.1, R32.2, R40.1, R51.2, R55.2, R60.2, R63.1, R72.1, R73.2, TP8.1, U1.1, U1.3, U1.15, U1.33, U1.40, U1.47, U1.52, U1.83, U2.2, U3.3, U3.8, U4.2, U6.4, U7.A2, U7.A3, U7.B4, U7.C4, U7.C5, U7.D4, U7.D5, U7.D6, U7.E3, U7.E4, U7.E5, U7.E6, U7.H8, U8.3, U8.8, U9.3, U9.8, U10.2, U11.2, U14.3, U14.8, U15.2, U16.8, U16.9, Y1.2; also elsewhere on the board
GPIO36: R12.1, U1.63
HDMI_5V: J2.18, R31.1, R67.1
HDMI_CEC: D1.1, J2.13, U7.G1
HDMI_HPD: J2.19, R30.2, R31.2, R32.1
HOST_CC1: J3.A5, R1.1
HOST_CC2: J3.B5, R2.1
HOST_VBUS: C50.1, J3.A4B9, J3.B4A9, R9.1
HOST_VBUS_DIV: R9.2, R10.1, U1.18
HPDI: R67.2, U7.H2
I2C_SCL: R23.1, U1.23, U7.H4
I2C_SDA: R22.1, U1.22, U7.G4
LCD_CLK: R81.1, U1.25
LCD_CLK_J: J6.4, R81.2
LCD_CS: J6.5, U1.26
LCD_DC: J6.6, U1.27
LCD_DIN: R80.1, U1.24
LCD_DIN_J: J6.3, R80.2
LCD_RST: J6.7, U1.28
LDO_VO4: C6.1, R41.1, R43.2, R44.2, R45.2, R46.2, R47.2, U1.66
LED_A: J4.6, R54.1
LED_IN: R54.2, U12.1
LED_K: J4.5, U12.2
LNA_OUT: J8.1, U1.2
OSC_OUT: C30.1, R24.1, Y1.3
OSC_VDD: C29.1, FB6.2, Y1.1, Y1.4
PWR_C: J4.1, U10.4
PWR_CC1: J5.A5, R3.1
PWR_CC2: J5.B5, R4.1
PWR_E: J4.2, U10.3
PWR_LED: R52.2, U10.1
RST_C: J4.3, U11.4
RST_E: J4.4, U11.3
RST_LED: R53.2, U11.1
SD1_VDD: C40.1, C41.1, J7.4, Q1.3
SD_CLK: R74.1, U1.71
SD_CLK_C: J7.5, R74.2
SD_CMD: R75.1, U1.72
SD_CMD_C: J7.3, R45.1, R75.2
SD_D0: R76.1, U1.67
SD_D0_C: J7.7, R46.1, R76.2
SD_D1: R77.1, U1.68
SD_D1_C: J7.8, R47.1, R77.2
SD_D2: R78.1, U1.69
SD_D2_C: J7.1, R43.1, R78.2
SD_D3: R79.1, U1.70
SD_D3_C: J7.2, R44.1, R79.2
SD_PWR_N: Q1.1, R40.2, U1.73
SD_SRC: Q1.2, R41.2, R42.2
SW: L1.1, U2.3
SW_1V2: L2.1, U15.3
TC_BIASDA: C25.1, U7.A4
TC_HPDO: R30.1, U7.H1
TC_PCKIN: C27.1, U7.B6
TC_PFIL: C26.1, U7.A6
TC_REFCLK: C31.1, R24.2, U7.H5
TC_REXT: R20.1, U7.A1
TC_RST: R21.2, U1.32, U7.G5
U0_RX: TP4.1, U1.65
U0_TX: TP3.1, U1.64
USB2_DN: J5.A7, J5.B7, U1.50, U14.2, U14.9
USB2_DP: J5.A6, J5.B6, U1.51, U14.1, U14.10
USB_DN: J3.A7, J3.B7, U1.48, U3.1, U3.10
USB_DP: J3.A6, J3.B6, R60.1, U1.49, U3.2, U3.9
V1V2: C12.1, C66.2, C67.2, FB3.1, FB4.1, FB5.1, L2.2, R65.2, R66.2
V1V2_SNS: R62.1, R65.1, R66.1
V2V5: C11.1, FB2.1, U4.5
VBUS_IN: C70.2, J5.A4B9, J5.B4A9, R71.1, U16.3, U16.4
VDDC: C19.1, C20.1, C21.1, FB5.2, U7.C3, U7.F5, U7.G2
VDD_MIPI: C17.1, C18.1, FB4.2, U7.C6, U7.F6
